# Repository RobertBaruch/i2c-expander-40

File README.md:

# I2C 40-I/O port expander #

## About ##

* It's a breakout board for the NXP PCA9698
* 40 I/O ports organized in 5 groups of 8
* 3.3v- and 5v-compatible
* Outputs source 10mA, sink 25mA at 5v
* Choose any of 64 I2C addresses, set via AD0-AD2 lines
* 100kHz, 400kHz and 1MHz I2C operation
* Open drain or totem-pole output
* Output enable, reset, and interrupt lines

This board isn't meant to go directly in breadboards. You can solder male or female headers either on the bottom of the board (preferred for installation as a daughter board on main boards) or on the top (preferred for prototyping or wiring to breadboards).

You will need two 2x20 headers and one 2x5 header.

Note that the I2C address is set by the AD0-AD2 lines which get connected to VSS, VDD, SDA, or SCL. See below, or the NXP PCA9698 datasheet section 7.15 for the address map. The table given in the datasheet shows columns A6-A0 and Address for each AD0-AD2 setting. The A6-A0 column gives you the _7-bit address_ that you must use from Arduinos, while the Address column shows the _8-bit address_.

## Files ##

* **i2c-expander-40-schematic.pdf:** The schematic in PDF format.
* **i2c-expander-40-gerbers.zip:** Contains Gerber files for board outline, top/bottom layers, top/bottom soldermask, top/bottom silkscreen, solder paste mask ("cream"), and drills. The files were generated from OSH Park's CAM processor for Eagle.
* **i2c-expander-40.brd, .sch:** Board and schematic files for Eagle (min version 7.5.0)
* **i2c-expander-40.lbr:** Library file containing devices used in the schematic and board, for Eagle (min version 7.5.0)

## AD2-AD0 7-bit address settings ##

Possible addresses are 0x10-0x2F, 0x50-0x67, 0x70-0x77.

Address | AD2 | AD1 | AD0 | Address | AD2 | AD1 | AD0
-------: | --- | --- | --- | -------: | --- | --- | ---
0x10 | Vss | SCL | Vss | 0x50 | SCL | SCL | Vss
0x11 | Vss | SCL | Vdd | 0x51 | SCL | SCL | Vdd
0x12 | Vss | SDA | Vss | 0x52 | SCL | SDA | Vss
0x13 | Vss | SDA | Vdd | 0x53 | SCL | SDA | Vdd
0x14 | Vdd | SCL | Vss | 0x54 | SDA | SCL | Vss
0x15 | Vdd | SCL | Vdd | 0x55 | SDA | SCL | Vdd
0x16 | Vdd | SDA | Vss | 0x56 | SDA | SDA | Vss
0x17 | Vdd | SDA | Vdd | 0x57 | SDA | SDA | Vdd
0x18 | Vss | SCL | SCL | 0x58 | SCL | SCL | SCL
0x19 | Vss | SCL | SDA | 0x59 | SCL | SCL | SDA
0x1A | Vss | SDA | SCL | 0x5A | SCL | SDA | SCL
0x1B | Vss | SDA | SDA | 0x5B | SCL | SDA | SDA
0x1C | Vdd | SCL | SCL | 0x5C | SDA | SCL | SCL
0x1D | Vdd | SCL | SDA | 0x5D | SDA | SCL | SDA
0x1E | Vdd | SDA | SCL | 0x5E | SDA | SDA | SCL
0x1F | Vdd | SDA | SDA | 0x5F | SDA | SDA | SDA
0x20 | Vss | Vss | Vss | 0x60 | SCL | Vss | Vss
0x21 | Vss | Vss | Vdd | 0x61 | SCL | Vss | Vdd
0x22 | Vss | Vdd | Vss | 0x62 | SCL | Vdd | Vss
0x23 | Vss | Vdd | Vdd | 0x63 | SCL | Vdd | Vdd
0x24 | Vdd | Vss | Vss | 0x64 | SDA | Vss | Vss
0x25 | Vdd | Vss | Vdd | 0x65 | SDA | Vss | Vdd
0x26 | Vdd | Vdd | Vss | 0x66 | SDA | Vdd | Vss
0x27 | Vdd | Vdd | Vdd | 0x67 | SDA | Vdd | Vdd
0x28 | Vss | Vss | SCL | 0x70 | SCL | Vss | SCL
0x29 | Vss | Vss | SDA | 0x71 | SCL | Vss | SDA
0x2A | Vss | Vdd | SCL | 0x72 | SCL | Vdd | SCL
0x2B | Vss | Vdd | SDA | 0x73 | SCL | Vdd | SDA
0x2C | Vdd | Vss | SCL | 0x74 | SDA | Vss | SCL
0x2D | Vdd | Vss | SDA | 0x75 | SDA | Vss | SDA
0x2E | Vdd | Vdd | SCL | 0x76 | SDA | Vdd | SCL
0x2F | Vdd | Vdd | SDA | 0x77 | SDA | Vdd | SDA

## Example commands ##

All values are hex.

### Write commands ###

* `ADDR 98 00 00 00 00 00` Sets the direction of ports 0-4 to output.
* `ADDR 9A 0F` Sets the direction of port 2 bits 3-0 to input.
* `ADDR 09 22` Writes 0x22 to port 1.
* `ADDR 88 11 22 33 44 55` Writes 0x11 to port 0, 0x22 to port 1, 0x33 to port 2, 0x44 to port 3, 0x55 to port 4.
* `ADDR 2A 00` Among other things, sets up the output change mode so that a multiport write causes outputs to change all at once after the command, rather than after each byte.

### Read commands ###

* `ADDR 0x00` Read from port 0. Every read will return the value of port 0.
* `ADDR 0x82` Read starting from port 2. Each read increments the port number, so you could read from port 2, port 3, and port 4 using this command.

## Example Arduino code ##

```C

#include "Wire.h"
#define ADDR 0x10

int setup() {
  Wire.begin(); // Set up Arduino as I2C master

  // Tell board at address 0x10 to set up ports 0-3 for output
  Wire.beginTransmission(ADDR);
  Wire.write({0x98, 0x00, 0x00, 0x00, 0x00}, 5);
  Wire.endTransmission();

  // Tell board at address 0x10 to set up port 4 for input
  Wire.beginTransmission(ADDR);
  Wire.write({0x9C, 0xFF}, 2);
  Wire.endTransmission();
}

int loop() {
  byte data;

  // Write 0x01 to port 0.
  Wire.beginTransmission(ADDR);
  Wire.write({0x08, 0x01}, 2);
  Wire.endTransmission();

  // Read port 4, several times in quick succession
  Wire.beginTransmission(ADDR);
  Wire.write({0x04}, 1);
  Wire.endTransmission();

  Wire.requestFrom(ADDR, 4);
  data = Wire.read();
  data = Wire.read();
  data = Wire.read();
  data = Wire.read();

  delay(1000);

  // Write 0x00 to port 0.
  Wire.beginTransmission(ADDR);
  Wire.write({0x08, 0x00}, 2);
  Wire.endTransmission();

  delay(1000);
}
```

## Further reading ##

* [NXP PCA9698 overview](http://www.nxp.com/products/interface-and-connectivity/interface-and-system-management/i2c/i2c-general-purpose-i-o/40-bit-fm-plus-i2c-bus-advanced-i-o-port-with-reset-oe-and-int:PCA9698)
* [NXP PCA9698 datasheet](http://www.nxp.com/documents/data_sheet/PCA9698.pdf)
* [Arduino Wire Library, Explored](http://playground.arduino.cc/Main/WireLibraryDetailedReference)

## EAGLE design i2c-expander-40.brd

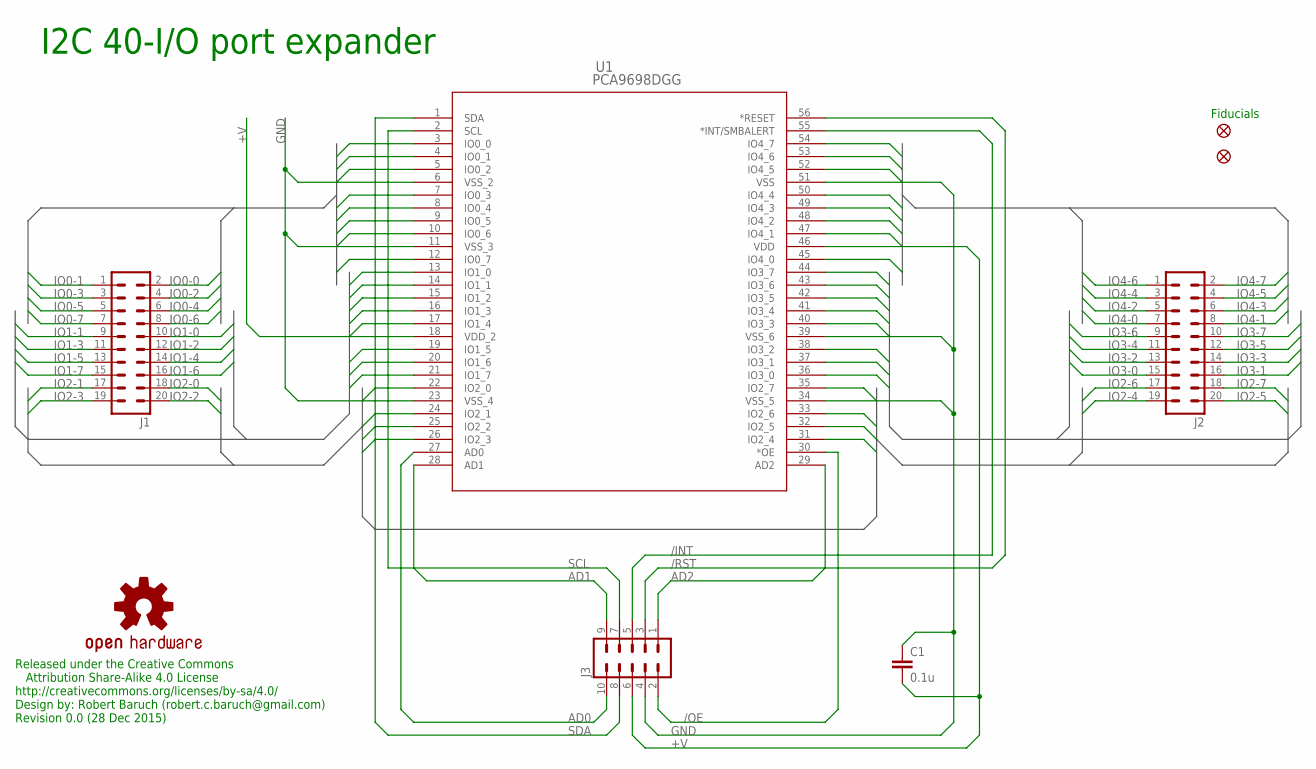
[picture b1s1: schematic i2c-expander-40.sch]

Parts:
C1: 0.1u; C0805K
FID1, FID2: FIDUCIAL1X2; FIDUCIAL-1X2
J1, J2: MA10-2
J3: MA05-2
LOGO1: OSHW-LOGOS; OSHW-LOGO-S
U1: PCA9698DGG; SOT364-1

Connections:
+V: C1.2, J3.6, U1.18 (VDD_2), U1.46 (VDD)
/INT: J3.5, U1.55 (*INT/SMBALERT)
/OE: J3.2, U1.30 (*OE)
/RST: J3.3, U1.56 (*RESET)
AD0: J3.10, U1.27 (AD0)
AD1: J3.9, U1.28 (AD1)
AD2: J3.1, U1.29 (AD2)
GND: C1.1, J3.4, U1.6 (VSS_2), U1.11 (VSS_3), U1.23 (VSS_4), U1.34 (VSS_5), U1.39 (VSS_6), U1.51 (VSS)
IO0-0: J1.2, U1.3 (IO0_0)
IO0-1: J1.1, U1.4 (IO0_1)
IO0-2: J1.4, U1.5 (IO0_2)
IO0-3: J1.3, U1.7 (IO0_3)
IO0-4: J1.6, U1.8 (IO0_4)
IO0-5: J1.5, U1.9 (IO0_5)
IO0-6: J1.8, U1.10 (IO0_6)
IO0-7: J1.7, U1.12 (IO0_7)
IO1-0: J1.10, U1.13 (IO1_0)
IO1-1: J1.9, U1.14 (IO1_1)
IO1-2: J1.12, U1.15 (IO1_2)
IO1-3: J1.11, U1.16 (IO1_3)
IO1-4: J1.14, U1.17 (IO1_4)
IO1-5: J1.13, U1.19 (IO1_5)
IO1-6: J1.16, U1.20 (IO1_6)
IO1-7: J1.15, U1.21 (IO1_7)
IO2-0: J1.18, U1.22 (IO2_0)
IO2-1: J1.17, U1.24 (IO2_1)
IO2-2: J1.20, U1.25 (IO2_2)
IO2-3: J1.19, U1.26 (IO2_3)
IO2-4: J2.19, U1.31 (IO2_4)
IO2-5: J2.20, U1.32 (IO2_5)
IO2-6: J2.17, U1.33 (IO2_6)
IO2-7: J2.18, U1.35 (IO2_7)
IO3-0: J2.15, U1.36 (IO3_0)
IO3-1: J2.16, U1.37 (IO3_1)
IO3-2: J2.13, U1.38 (IO3_2)
IO3-3: J2.14, U1.40 (IO3_3)
IO3-4: J2.11, U1.41 (IO3_4)
IO3-5: J2.12, U1.42 (IO3_5)
IO3-6: J2.9, U1.43 (IO3_6)
IO3-7: J2.10, U1.44 (IO3_7)
IO4-0: J2.7, U1.45 (IO4_0)
IO4-1: J2.8, U1.47 (IO4_1)
IO4-2: J2.5, U1.48 (IO4_2)
IO4-3: J2.6, U1.49 (IO4_3)
IO4-4: J2.3, U1.50 (IO4_4)
IO4-5: J2.4, U1.52 (IO4_5)
IO4-6: J2.1, U1.53 (IO4_6)
IO4-7: J2.2, U1.54 (IO4_7)
SCL: J3.7, U1.2 (SCL)
SDA: J3.8, U1.1 (SDA)

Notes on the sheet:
Released under the Creative Commons Attribution Share-Alike 4.0 License http://creativecommons.org/licenses/by-sa/4.0/ Design by: Robert Baruch (robert.c.baruch@gmail.com) Revision 0.0 (28 Dec 2015)
Fiducials
I2C 40-I/O port expander

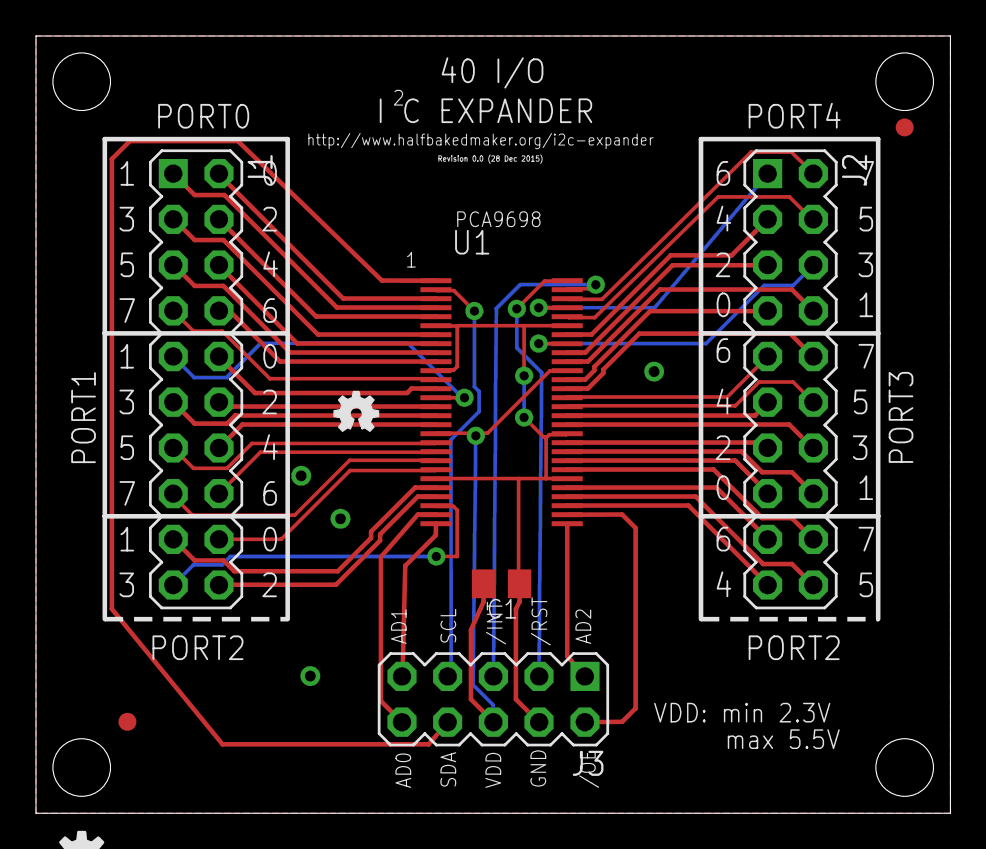
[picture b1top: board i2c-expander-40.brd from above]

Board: 2 copper layers, 50.8 x 43.2 mm, 9 parts (0 on the bottom side), 50 nets.

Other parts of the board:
U$1: OSHW-LOGO-MINI

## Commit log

2015-12-30 Adds revision 0 files
2015-12-30 Corrects address map

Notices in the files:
parts and their libraries:
SparkFun-Aesthetics: Licensing: Creative Commons ShareAlike 4.0 International - https://creativecommons.org/licenses/by-sa/4.0
COPYRIGHT: Copyright (C) 2015 Accelerated Designs. All rights reserved
